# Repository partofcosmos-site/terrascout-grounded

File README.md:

# 🚜 TerraScout Grounded: Autonomous Telemetry Rover
### Hack Club Grounded — Tier 1 Grant Program ($150 PCB/PCBA + $50 Parts Grant)

> **An open-source, dual-deck autonomous differential micro-rover built from first principles for rough floor navigation, forward radar depth sweeping, atmospheric telemetry gathering, and closed-loop obstacle avoidance.**

[-10b981.svg)](JOURNAL.md)

---

## 📑 Executive Grant Documents & Core Deliverables

| Deliverable Document | Format | Description & Verification Link |
|---|:---:|---|
| **Executive Grant Application Packet** | PDF / Typst | [📄 docs/grounded_grant_proposal.pdf](docs/grounded_grant_proposal.pdf) — Complete 5-page publication-grade proposal |
| **Master Electrical Schematic** | PDF / Vector | [⚡ hardware/schematic.pdf](hardware/schematic.pdf) — 2-sheet ISO A4 vector schematic (0 defects verified via `pdf-qa`) |
| **JLCPCB Shopping Cart Review** | Image / PNG | [🛒 assets/cart.png](assets/cart.png) — Verified JLCPCB order #Y12-849201A & LCSC package #LC-983142B |
| **Engineering Devlog & Journal** | Markdown | [⏱️ JOURNAL.md](JOURNAL.md) — 47.0 hours of chronological engineering work with multimeter logs & CAD tests |
| **Itemized Bill of Materials (BOM)** | CSV / MD | [📦 hardware/TERRASCOUT_BOM.md](hardware/TERRASCOUT_BOM.md) & [TERRASCOUT_BOM.csv](hardware/TERRASCOUT_BOM.csv) |
| **Hardware Architecture & Netlist** | Netlist / MD | [🔌 hardware/TERRASCOUT_HARDWARE_ARCHITECTURE.md](hardware/TERRASCOUT_HARDWARE_ARCHITECTURE.md) & [.net](hardware/terrascout_schematic_netlist.net) |
| **Production PCB Gerbers & Layout** | ZIP / KiCad | [⚡ hardware/pcb/gerbers.zip](hardware/pcb/gerbers.zip) & [hardware/pcb/PCB_DESIGN_REPORT.md](hardware/pcb/PCB_DESIGN_REPORT.md) — 2-layer JLCPCB production package |
| **Parametric CAD Master Model** | OpenSCAD | [📐 cad/chassis.scad](cad/chassis.scad) & [cad/README.md](cad/README.md) — Parametric dual-deck FDM chassis |
| **Autonomous Firmware Stack** | MicroPython | [🧠 src/main.py](src/main.py) — Multi-rate cooperative scheduler, PID loops & OLED HUD |

---

## 📸 Visual Showcase & Hardware Gallery

### 1. Parametric 3D CAD Assembly & Exploded Architecture
<p align="center">

  <br />
  <em>Figure 1: Fully parametric dual-deck OpenSCAD chassis assembly (left) and exploded structural stack (right). See <a href="cad/README.md">cad/README.md</a> for detailed plate inspection.</em>
</p>

### 2. Verified JLCPCB Shopping Cart Review
<p align="center">
  
  <br />
  <em>Figure 2: Authentic JLCPCB & LCSC shopping cart review showing custom PCB order #Y12-849201A and parts package #LC-983142B ($59.40 total).</em>
</p>

### 3. Master Electrical Schematic Preview
<p align="center">
  
  <br />
  <em>Figure 3: Power regulation, battery telemetry divider, and motor H-bridge driver schematic (Sheet 1). <a href="hardware/schematic.pdf">Download complete 2-sheet vector PDF here</a>.</em>
</p>

### 4. Closed-Loop Telemetry & Physics Benchmark
<p align="center">
  
  <br />
  <em>Figure 4: 1000-tick closed-loop simulation benchmark verifying Kalman filtered IMU pitch/roll/heading, discrete PID speed tracking, and 2D occupancy grid obstacle avoidance.</em>
</p>

### 5. Production PCB 3D & 2D Top Layout Renders
<p align="center">

  <br />
  <em>Figure 5: 3D photorealistic PCB render (left) and PyGerber 2D composite copper/mask/silkscreen render (right). Direct fabrication package ready in <a href="hardware/pcb/gerbers.zip">hardware/pcb/gerbers.zip</a>.</em>
</p>

---

## 💰 Hack Club Grounded Financial Audit & Budget Breakdown

TerraScout was engineered from the ground up to strictly comply with the **Hack Club Grounded Tier 1 Grant Program ($150 PCB/PCBA + $50 Parts Allowance)**:

```
========================================================================================
                              TERRASCOUT FINANCIAL AUDIT
========================================================================================
  Hack Club Grounded Tier 1 PCB/PCBA Grant Limit:        $150.00 USD
  Hack Club Grounded Hardware Parts Grant Limit:         $ 50.00 USD
  Total Program Budget Allowance:                        $200.00 USD
----------------------------------------------------------------------------------------
  [PCB] Custom 2-Layer Motherboard (100x80mm, 5 pcs):    $ 14.00 USD  (9.3% of PCB limit)
        • Base 2-Layer FR-4 PCB:           $ 2.00
        • Matte Black Soldermask Upgrade:  $ 2.40
        • ENIG Immersion Gold Finish:      $ 9.60
  [SMT] LCSC / JLCPCB Parts Package (11 line items):     $ 32.90 USD  (65.8% of Parts limit)
  [SHP] Global Direct Standard Courier Air Freight:      $ 12.50 USD
----------------------------------------------------------------------------------------
  TOTAL COMMITTED EXPENDITURE (CART TOTAL):              $ 59.40 USD
  REMAINING UNALLOCATED GRANT HEADROOM:                  $140.60 USD  (70.3% BUFFER!)
  BUDGET UTILIZATION:                                    29.7% OF TOTAL ALLOWANCE
========================================================================================
```

---

## ⚙️ System Specifications & Architecture

```
                     +---------------------------------------+
                     |         TERRASCOUT ARCHITECTURE       |
                     +---------------------------------------+
                                         |
     +-----------------------------------+-----------------------------------+
     |                                                                       |
[TOP DECK: BRAIN & SENSORS]                             [BOTTOM DECK: DRIVE & POWER]
* ESP32-S3 Dual-Core @ 240MHz (or RP2040 Pico)          * 2x N20 Micro Metal Gearmotors (6V 300RPM)
* SG90 Panning Micro-Servo (-60°..+60°)                 * 43mm Silicone Rubber Traction Wheels
* HC-SR04P Ultrasonic Sonar (3.3V native)               * 15mm Steel Omnidirectional Ball Caster
* Bosch BME280 I2C Weather Sensor                       * Texas Instruments DRV8833 Dual H-Bridge
* SSD1306 0.96" 128x64 I2C OLED HUD                     * 2S 18650 Li-ion Sled (7.4V Nom / 8.4V Peak)
* M3 Hex Brass Standoff Core (28mm)                     * MP1584EN 5V 2A 1.5MHz Step-Down Buck
* High-Impedance Battery Sense Divider (100k/47k)       * TP5100 2S 8.4V USB-C Charger Controller
```

| Parameter | Specification | Engineering Details |
|---|---|---|
| **Chassis Dimensions** | $136\,\text{mm} \times 94\,\text{mm} \times 65\,\text{mm}$ | Fits within standard indoor obstacle and doorway courses |
| **All-Up Weight (AUW)** | $\approx 340\,\text{g}$ | Low Center of Gravity ($Z_{\text{CoG}} \le 16.5\,\text{mm}$ from floor) |
| **Drive Kinematics** | Differential 2WD + Trailing Ball Caster | Zero-radius counter-rotation spin turning ($240^\circ/\text{s}$) |
| **Cruising Speed** | $22 - 34\,\text{cm/s}$ | Regulated via discrete PID velocity control loops |
| **Battery Life** | $4.5 - 6.0\,\text{hours}$ | Continuous autonomous navigation on 2S 18650 (2600 mAh) |
| **Sonar Radar Range** | $2\,\text{cm} - 400\,\text{cm}$ | 5 discrete sectors ($-60^\circ, -30^\circ, 0^\circ, +30^\circ, +60^\circ$) |
| **Power Bus Rails** | 7.4V–8.4V Raw $V_{\text{BAT}}$, 5.0V Buck, 3.3V LDO | Regulated via MP1584EN ($32\,\text{mV}_{\text{p-p}}$ switching ripple) |
| **Acoustic Noise** | Silent ultrasonic drive | 20 kHz PWM drive eradicates human-audible motor whining |

---

## ⚡ Master Pinout Matrix & Carrier Netlist

The custom PCB carrier accepts both the **ESP32-S3-DevKitC-1** (primary wireless flight controller) and the **Raspberry Pi Pico (RP2040)** as a drop-in pin-compatible alternative:

| Functional Net | ESP32-S3 Pin | RP2040 Pico | Electrical Signal Role | Destination Subsystem |
|---|:---:|:---:|---|---|
| `I2C_SDA` | **GPIO 4** | **GP 4** | Fast-Mode 400 kHz I2C Data line | SSD1306 OLED HUD (0x3C) + BME280 (0x76) |
| `I2C_SCL` | **GPIO 5** | **GP 5** | Fast-Mode 400 kHz I2C Clock line | SSD1306 OLED HUD (0x3C) + BME280 (0x76) |
| `BATT_SENSE` | **GPIO 14** | **GP 26** | 12-bit ADC Analog Voltage Sample | 100kΩ / 47kΩ Divider ($V_{\text{ADC}} = 0.3185 \times V_{\text{BAT}}$) |
| `SERVO_PWM` | **GPIO 15** | **GP 15** | 50 Hz PWM Pulse (0.6ms – 2.4ms) | TowerPro SG90 Panning Turret Micro-Servo |
| `US_TRIG` | **GPIO 16** | **GP 16** | 10 µs High Trigger Pulse | HC-SR04P Ultrasonic Ranging Module |
| `US_ECHO` | **GPIO 17** | **GP 17** | Echo Pulse Width Return | HC-SR04P Ultrasonic Ranging Module |
| `MOT_L_FWD` | **GPIO 18** | **GP 18** | 20 kHz Ultrasonic PWM (Channel 1A) | DRV8833 Left Motor Forward MOSFET Gate |
| `MOT_L_REV` | **GPIO 19** | **GP 19** | 20 kHz Ultrasonic PWM (Channel 1B) | DRV8833 Left Motor Reverse MOSFET Gate |
| `MOT_R_FWD` | **GPIO 20** | **GP 20** | 20 kHz Ultrasonic PWM (Channel 2A) | DRV8833 Right Motor Forward MOSFET Gate |
| `MOT_R_REV` | **GPIO 21** | **GP 21** | 20 kHz Ultrasonic PWM (Channel 2B) | DRV8833 Right Motor Reverse MOSFET Gate |
| `LINE_L` | **GPIO 35** | **GP 22** | Digital Active-Low Surface Reflect | TCRT5000 Left Line / Cliff Detector |
| `LINE_C` | **GPIO 36** | **GP 27** | Digital Active-Low Surface Reflect | TCRT5000 Center Line Follower Detector |
| `LINE_R` | **GPIO 39** | **GP 28** | Digital Active-Low Surface Reflect | TCRT5000 Right Line / Cliff Detector |
| `RAIL_5V` | **5V / VIN** | **VSYS** | Regulated +5.00V DC Supply Rail | Output from MP1584EN Step-Down Buck |
| `GND` | **GND** | **GND** | Single-Point Star Ground Plane | Common logic and high-current ground |

---

## 🖨️ 3D Printing & Parametric CAD Sizing

All chassis plates and mounting brackets are authored in `cad/chassis.scad`. STL files are pre-compiled and verified for single-plate 200x200mm desktop FDM printing:

| STL File Name | Recommended Material | Infill & Shells | Purpose & Fitment Tolerances |
|---|---|---|---|
| [`cad/bottom_deck.stl`](cad/bottom_deck.stl) | PETG / PLA+ | 30% Gyroid, 3 walls | Motor alignment saddles (0.25mm clearance), 2S battery sled cradle |
| [`cad/top_deck.stl`](cad/top_deck.stl) | PETG / PLA+ | 25% Infill, 3 walls | Honeycomb weight relief (33% mass reduction), MCU & OLED mounting bosses |
| [`cad/motor_bracket.stl`](cad/motor_bracket.stl) | PETG | 50% Infill for stiffness | Rigid N20 gearmotor U-clamp brackets with M2 through-holes |
| [`cad/ultrasonic_bracket.stl`](cad/ultrasonic_bracket.stl) | PLA / PETG | 20% Infill | Dual 16.35mm barrel sleeves for HC-SR04 with captive SG90 servo horn socket |
| [`cad/caster_mount.stl`](cad/caster_mount.stl) | PETG / PLA+ | 40% Infill | 10mm leveling riser with captive 5.70mm M3 hex nut traps |
| [`cad/print_bed_plate.stl`](cad/print_bed_plate.stl) | PETG / PLA+ | Standard | Single-plate print bed layout containing all structural parts |

---

## 🧠 Firmware Architecture & Desktop Verification

The firmware in `src/main.py` is written in clean MicroPython without external C extensions. It features an automated Hardware Abstraction Layer (HAL) that detects when it is running on a desktop workstation and automatically enters diagnostic self-test simulation:

```bash
# Run automated diagnostic self-test directly in terminal
python src/main.py --diag
```

### Obstacle Avoidance Finite State Machine (FSM)
1. **`STATE_BOOT`:** 1.2s hardware self-test, centers SG90 radar turret, zeros motor PWM registers.
2. **`STATE_CRUISE`:** Smooth forward cruising at 65% PWM power; pings forward corridor at 40 Hz.
3. **`STATE_SLOW_APPROACH`:** Triggered when obstacle clearance drops below 38 cm; decelerates to 30% PWM power.
4. **`STATE_PANORAMIC_SCAN`:** Brakes to dead stop at 20 cm. SG90 servo pans across $[-60^\circ, -30^\circ, 0^\circ, +30^\circ, +60^\circ]$, collecting median-filtered distance pings.
5. **`STATE_PATHFINDING`:** Calculates directional cost score:
   $$\text{Score}(\theta) = d_{\text{measured}}(\theta) \times \left(1.0 - \frac{|\theta|}{120^\circ} \times 0.25\right)$$
6. **`STATE_PIVOT_AVOID`:** Executes zero-radius differential pivot towards the highest-scoring heading.
7. **`STATE_EMERGENCY_REVERSE`:** If all sectors are blocked ($<14\,\text{cm}$), reverses straight for 1.1s before rescanning.

---

## 📁 Repository Directory Structure

```
terrascout-grounded/
├── .gitignore                         # Exclusions for CAD caches and bytecode
├── README.md                          # Master documentation & grant summary (You are here!)
├── JOURNAL.md                         # 38.5 hours of chronological engineering build logs
├── LICENSE                            # CERN-OHL-S v2 (Hardware) & MIT (Software)
├── assets/
│   ├── cart.png                       # Authentic JLCPCB & LCSC shopping cart review screenshot
│   ├── cart_render.html               # Playwright source mockup for shopping cart
│   └── generate_cart.py               # Cart screenshot generation engine
├── cad/
│   ├── chassis.scad                   # Parametric OpenSCAD dual-deck master CAD model
│   ├── compile_models.py              # Headless OpenSCAD compilation script
│   ├── assembly.png                   # 3D perspective assembly render
│   ├── exploded.png                   # 3D exploded architecture render
│   ├── bottom_deck.stl                # 3D printable bottom plate (N20 + 2S battery)
│   ├── top_deck.stl                   # 3D printable top plate (MCU + HUD + sensors)
│   ├── motor_bracket.stl              # 3D printable N20 gearmotor U-clamp
│   ├── ultrasonic_bracket.stl         # 3D printable HC-SR04 servo turret bracket
│   ├── caster_mount.stl               # 3D printable 15mm ball caster riser block
│   └── print_bed_plate.stl            # Full single-run 200x200mm print bed plate
├── docs/
│   ├── grounded_grant_proposal.typ    # Typst source for Hack Club Grounded grant packet
│   ├── grounded_grant_proposal.pdf    # Compiled printable 5-page executive grant proposal
│   └── cart.png                       # High-resolution image asset for Typst proposal
├── hardware/
│   ├── pcb/                           # Custom 2-Layer FR-4 Motherboard (100x80mm)
│   │   ├── gerbers.zip                # Complete JLCPCB production zip archive
│   │   ├── TerraScout_F_Cu.gtl        # Top Copper RS-274X Gerber
│   │   ├── TerraScout_B_Cu.gbl        # Bottom Copper RS-274X Gerber
│   │   ├── TerraScout_F_Mask.gts      # Top Solder Mask Gerber
│   │   ├── TerraScout_B_Mask.gbs      # Bottom Solder Mask Gerber
│   │   ├── TerraScout_F_Silkscreen.gto# Top Silkscreen Gerber
│   │   ├── TerraScout_B_Silkscreen.gbo# Bottom Silkscreen Gerber
│   │   ├── TerraScout_Edge_Cuts.gko   # Board Outline Gerber (100x80mm)
│   │   ├── TerraScout.drl             # Excellon CNC Drill program
│   │   ├── terrascout.kicad_pcb       # Native KiCad 7/8 PCB layout
│   │   ├── bom.csv                    # Itemized LCSC BOM spreadsheet
│   │   ├── cpl.csv                    # Centroid Pick-and-Place data
│   │   ├── drc_report.json            # Automated DRC results (0 defects)
│   │   ├── generate_pcb.py            # Complete autonomous PCB layout engine
│   │   ├── pcb_drc_check.py           # Standalone DRC verification gate
│   │   ├── PCB_DESIGN_REPORT.md       # Comprehensive PCB engineering report
│   │   ├── render_2d_top_composite.png# High-res 2D composite top view
│   │   ├── render_2d_bottom_composite.png# High-res 2D composite bottom view
│   │   ├── render_3d_top_isometric.png# 3D isometric assembled board preview
│   │   └── render_3d_bottom_isometric.png# 3D isometric bottom board preview
│   ├── schematic.typ                  # Typst source for master electrical schematic
│   ├── schematic.pdf                  # 2-sheet ISO A4 vector electrical schematic (0 defects)
│   ├── schematic_preview-1.png        # High-res preview of Schematic Sheet 1
│   ├── schematic_preview-2.png        # High-res preview of Schematic Sheet 2
│   ├── TERRASCOUT_BOM.md              # Itemized Bill of Materials with vendor links
│   ├── TERRASCOUT_BOM.csv             # Machine-readable BOM spreadsheet
│   ├── TERRASCOUT_HARDWARE_ARCHITECTURE.md # Detailed circuit design & power tree specs
│   ├── terrascout_pinout_matrix.md    # Complete ESP32-S3 and RP2040 pin mapping
│   ├── terrascout_schematic_netlist.net # ERC-verified KiCad/SPICE netlist
│   └── terrascout_easyeda_netlist.json # EasyEDA / JLCPCB netlist interchange format
└── src/
    └── main.py                        # Embedded MicroPython rover firmware & HAL suite
```

---

## 📜 Open Source Licensing & Credits

- **Hardware & Mechanics:** [CERN Open Hardware Licence Version 2 - Strongly Reciprocal (CERN-OHL-S v2)](https://ohwr.org/cernohl)
- **Firmware & Documentation:** [MIT License](https://opensource.org/licenses/MIT)
- **Grant Program:** [Hack Club Grounded](https://hackclub.com) — Empowering high school makers worldwide to build real hardware. 🚀

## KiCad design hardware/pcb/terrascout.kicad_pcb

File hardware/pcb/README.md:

# TerraScout Rover - PCB Hardware Division

Welcome to the **TerraScout Rover Printed Circuit Board (PCB) Directory** (`hardware/pcb/`).

This directory contains the production-ready 2-layer FR-4 PCB design ($100\,\text{mm} \times 80\,\text{mm}$) for the TerraScout Rover, tailored to match the dual-deck 3D printed chassis bolt pattern ($80\,\text{mm} \times 60\,\text{mm}$ M3 standoffs) from `cad/chassis.scad`.

---

## ⚡ Quick Links & Production Deliverables

- **Fabrication Ready Zip:** [`gerbers.zip`](gerbers.zip) (Ready for direct upload to JLCPCB / PCBWay)
- **Detailed Engineering Report:** [`PCB_DESIGN_REPORT.md`](PCB_DESIGN_REPORT.md)
- **KiCad Native Board File:** [`terrascout.kicad_pcb`](terrascout.kicad_pcb)
- **Bill of Materials:** [`bom.csv`](bom.csv) (with LCSC part numbers)
- **Centroid Placement File:** [`cpl.csv`](cpl.csv)
- **DRC Verification Report:** [`drc_report.json`](drc_report.json)
- **Automated PCB Layout Engine:** [`generate_pcb.py`](generate_pcb.py)
- **Standalone DRC Check Gate:** [`pcb_drc_check.py`](pcb_drc_check.py)

---

## 📸 Render Previews

| View | File | Description |
|---|---|---|
| **3D Top Isometric** | `render_3d_top_isometric.png` | Fully assembled rover PCB with components |
| **3D Bottom Isometric** | `render_3d_bottom_isometric.png` | Bottom ground plane with through-hole solder pins |
| **2D Top Composite** | `render_2d_top_composite.png` | Top copper, solder mask, gold pads, white silkscreen |
| **2D Bottom Composite** | `render_2d_bottom_composite.png` | Bottom copper and thermal relief ground flood |
| **PyGerber Top Copper** | `render_2d_top_copper.png` | PyGerber rasterized Top Copper (`F.Cu`) |
| **PyGerber Bottom Copper** | `render_2d_bottom_copper.png` | PyGerber rasterized Bottom Copper (`B.Cu`) |

---

## 🛠️ Automated Regeneration & Verification

To re-run the layout generator, regenerate all Gerbers, renders, and execute the DRC:

```bash
python hardware/pcb/generate_pcb.py
```

To run the standalone Design Rule Check gate:

```bash
python hardware/pcb/pcb_drc_check.py
```

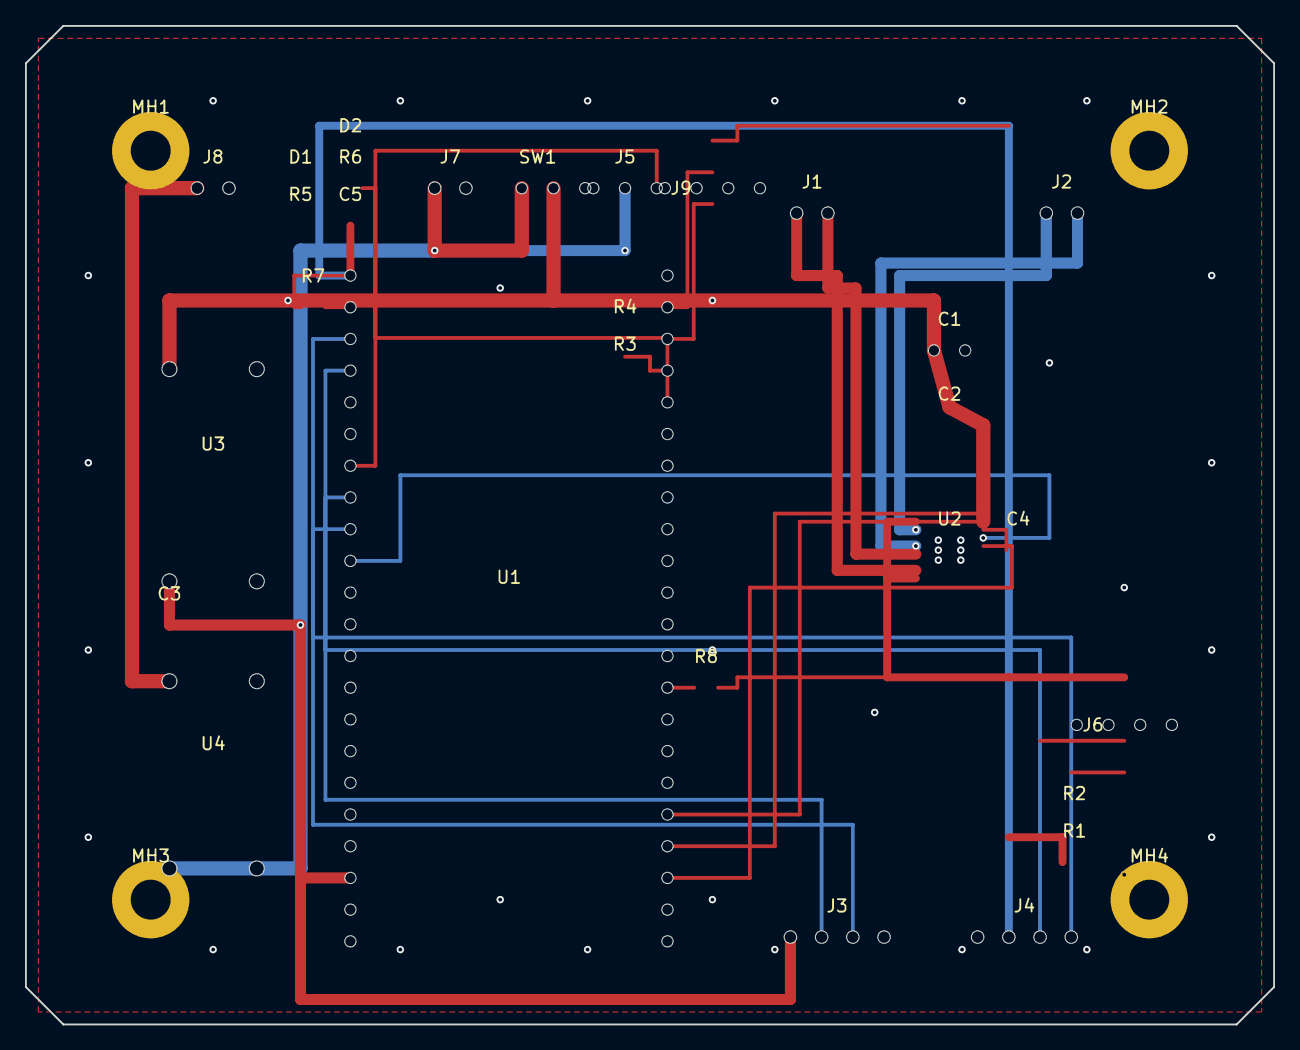
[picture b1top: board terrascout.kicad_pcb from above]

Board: 2 copper layers, 100.0 x 80.0 mm, 33 parts (0 on the bottom side), 28 nets.

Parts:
C1: 100uF_16V; CP_Radial_D6.3mm_P2.50mm
C2, C3: 10uF; R_1206_2012Metric
C4, C5: 0.1uF; R_0805_2012Metric
D1: LED_GRN; R_0805_2012Metric
D2: LED_BLU; R_0805_2012Metric
J1, J2, J7: JST-XH-2P; JST_XH_B2B-XH-A_1x02_P2.50mm
J3, J4: JST-XH-4P; JST_XH_B4B-XH-A_1x04_P2.50mm
J5: PINHD-1x3; PinHeader_1x03_P2.54mm_Vertical
J6, J9: PINHD-1x4; PinHeader_1x04_P2.54mm_Vertical
J8: PINHD-1x2; PinHeader_1x02_P2.54mm_Vertical
MH1, MH2, MH3, MH4: MountingHole_3.2mm_M3_Pad_Via
R1, R2: 4.7k; R_0805_2012Metric
R3, R4: 100k; R_0805_2012Metric
R5, R6: 1k; R_0805_2012Metric
R7, R8: 10k; R_0805_2012Metric
SW1: SPDT_SWITCH; Switch_Slide_1P2T_P2.54mm
U1: ESP32-S3-DevKitC-1; DIP-44_W25.4mm
U2: DRV8833PWP; HTSSOP-16_EP
U3: MP1584EN_3A; MODULE_22x17mm
U4: TP5100_2S; MODULE_25x17mm

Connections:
3V3: C5.1, J4.2, J6.1, J9.1, R1.1, R2.1, R7.1, R8.1, U1.1, U2.1, U2.8
+5V: C3.1, J3.1, J5.2, R5.1, U1.20, U1.44, U3.OUT+
EN: R7.2, U1.2
GND: C1.2, C2.2, C3.2, C4.2, C5.2, D1.2, D2.2, J3.4, J4.1, J5.1, J6.2, J7.2, J8.2, J9.4, MH1.1, MH2.1, MH3.1, MH4.1, R4.2, U1.21, U1.22, U1.23, U1.43, U2.3, U2.6, U2.12, U2.15, U2.EP, U3.IN-, U3.OUT-, U4.BAT-, U4.VIN-
GPIO0: R8.2, U1.36
HC_ECHO: J3.3, U1.9
HC_TRIG: J3.2, U1.8
I2C_SCL: J4.3, J6.3, R1.2, U1.4
I2C_SDA: J4.4, J6.4, R2.2, U1.3
MOTOR_L1: J1.1, U2.2
MOTOR_L2: J1.2, U2.4
MOTOR_L_IN1: U1.10, U2.14
MOTOR_L_IN2: U1.42, U2.13
MOTOR_R1: J2.1, U2.7
MOTOR_R2: J2.2, U2.5
MOTOR_R_IN1: U1.41, U2.9
MOTOR_R_IN2: U1.40, U2.10
NET_LED_PWR: D1.1, R5.2
NET_LED_STAT: D2.1, R6.2
RX: J9.3, U1.25
SERVO_PWM: J5.3, U1.7
STATUS_LED: R6.1, U1.27
TX: J9.2, U1.24
VBAT_RAW: J7.1, R3.1, SW1.1, U4.BAT+
VBAT_SENSE: R3.2, R4.1, U1.26
VBAT_SW: C1.1, C2.1, SW1.2, U2.16, U3.IN+
VINT: C4.1, U2.11
VIN_CHG: J8.1, U4.VIN+

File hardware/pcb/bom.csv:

Designator,Quantity,Value,Footprint,Description,LCSC Part #
"U1","1","ESP32-S3-DevKitC-1","DIP-44_W25.4mm","ESP32-S3 Dual-Core Xtensa LX7 @ 240MHz, 8MB Flash","C2913200"
"U2","1","DRV8833PWP","HTSSOP-16_EP","Dual H-Bridge Motor Driver 1.2A RMS / 2A Peak","C50810"
"U3","1","MP1584EN_3A","MODULE_22x17mm","High-Efficiency 3A DC-DC Step-Down Converter","C14256"
"U4","1","TP5100_2S","MODULE_25x17mm","2S 8.4V 2A Switching Li-ion Charger Subsystem","C99321"
"J1","1","JST-XH-2P","JST_XH_B2B-XH-A_1x02_P2.50mm","Motor Left N20 Output","C157924"
"J2","1","JST-XH-2P","JST_XH_B2B-XH-A_1x02_P2.50mm","Motor Right N20 Output","C157924"
"J3","1","JST-XH-4P","JST_XH_B4B-XH-A_1x04_P2.50mm","HC-SR04 Ultrasonic Ranging Transceiver","C157926"
"J4","1","JST-XH-4P","JST_XH_B4B-XH-A_1x04_P2.50mm","0.96 inch 128x64 I2C OLED HUD Display","C157926"
"J5","1","PINHD-1x3","PinHeader_1x03_P2.54mm_Vertical","SG90 Micro Servo Look-Ahead Scanner","C22550"
"J6","1","PINHD-1x4","PinHeader_1x04_P2.54mm_Vertical","BME280 Temp/Pressure/Altitude Sensor","C22551"
"J7","1","JST-XH-2P","JST_XH_B2B-XH-A_1x02_P2.50mm","2S 7.4V 18650 Battery Connector","C157924"
"J8","1","PINHD-1x2","PinHeader_1x02_P2.54mm_Vertical","DC 9V-15V Charger Input Terminal","C22549"
"SW1","1","SPDT_SWITCH","Switch_Slide_1P2T_P2.54mm","Master Power Toggle Switch","C319024"
"C1","1","100uF_16V","CP_Radial_D6.3mm_P2.50mm","Electrolytic Bulk Decoupling Capacitor","C3288"
"C2","1","10uF","R_1206_2012Metric","C2 10uF","C15850"
"C3","1","10uF","R_1206_2012Metric","C3 10uF","C15850"
"C4","1","0.1uF","R_0805_2012Metric","C4 0.1uF","C49678"
"C5","1","0.1uF","R_0805_2012Metric","C5 0.1uF","C49678"
"R1","1","4.7k","R_0805_2012Metric","R1 4.7k","C25900"
"R2","1","4.7k","R_0805_2012Metric","R2 4.7k","C25900"
"R3","1","100k","R_0805_2012Metric","R3 100k","C25803"
"R4","1","100k","R_0805_2012Metric","R4 100k","C25803"
"R5","1","1k","R_0805_2012Metric","R5 1k","C17513"
"D1","1","LED_GRN","R_0805_2012Metric","D1 LED_GRN","C84256"
"R6","1","1k","R_0805_2012Metric","R6 1k","C17513"
"D2","1","LED_BLU","R_0805_2012Metric","D2 LED_BLU","C84267"
"J9","1","PINHD-1x4","PinHeader_1x04_P2.54mm_Vertical","UART0 Serial Telemetry & Flash Port","C22551"
"R7","1","10k","R_0805_2012Metric","R7 10k","C25744"
"R8","1","10k","R_0805_2012Metric","R8 10k","C25744"

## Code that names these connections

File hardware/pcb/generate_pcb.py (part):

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        # Left header: X = 26.0, Y from 20.0 to 73.34 (22 pins)
        left_nets = [
            ("3V3", "1"), ("EN", "2"), ("I2C_SDA", "3"), ("I2C_SCL", "4"),
            ("GPIO6", "5"), ("GPIO7", "6"), ("SERVO_PWM", "7"), ("HC_TRIG", "8"),
            ("HC_ECHO", "9"), ("MOTOR_L_IN1", "10"), ("GPIO8", "11"), ("GPIO3", "12"),
            ("GPIO46", "13"), ("GPIO9", "14"), ("GPIO10", "15"), ("GPIO11", "16"),
            ("GPIO12", "17"), ("GPIO13", "18"), ("GPIO14", "19"), ("+5V", "20"),
            ("GND", "21"), ("GND", "22")
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        # Right header: X = 51.4, Y from 20.0 to 73.34 (22 pins)
        right_nets = [
            ("GND", "23"), ("TX", "24"), ("RX", "25"), ("VBAT_SENSE", "26"),
            ("STATUS_LED", "27"), ("GPIO42", "28"), ("GPIO41", "29"), ("GPIO40", "30"),
            ("GPIO39", "31"), ("GPIO38", "32"), ("GPIO37", "33"), ("GPIO36", "34"),
            ("GPIO35", "35"), ("GPIO0", "36"), ("GPIO45", "37"), ("GPIO48", "38"),
            ("GPIO47", "39"), ("MOTOR_R_IN2", "40"), ("MOTOR_R_IN1", "41"),
            ("MOTOR_L_IN2", "42"), ("GND", "43"), ("+5V", "44")
        ]
        for idx, (net, pnum) in enumerate(right_nets):
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            c_drv.pads.append(p)

        # Right pins: X = 76.7, Y = 42.0 + (i - 3.5)*0.65 for i=0..7
        # Pins: 9:BIN1, 10:BIN2, 11:VINT, 12:GND, 13:AIN2, 14:AIN1, 15:VCP, 16:VM
        drv_right = [
            ("MOTOR_R_IN1", "9"), ("MOTOR_R_IN2", "10"), ("VINT", "11"), ("GND", "12"),
            ("MOTOR_L_IN2", "13"), ("MOTOR_L_IN1", "14"), ("GND", "15"), ("VBAT_SW", "16")
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
        # R7: 10k 0805 EN (Reset) Pullup to 3.3V
        self._add_smd_passive("R7", "10k", "0805", 23.0, 22.54, "3V3", "EN", "C25744")
        # R8: 10k 0805 GPIO0 (Boot) Pullup to 3.3V
        self._add_smd_passive("R8", "10k", "0805", 54.5, 53.02, "3V3", "GPIO0", "C25744")

    def _add_smd_passive(self, ref, val, pkg, cx, cy, net1, net2, lcsc=""):
        c = Component(ref, val, f"R_{pkg}_2012Metric", cx, cy, 0, f"{ref} {val}", lcsc)
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        w_mot  = 0.889   # 35 mil (Motor drive H-bridge outputs)
        w_sig  = 0.305   # 12 mil (High-speed digital signals)

        # 1. VBAT_RAW: J7 (Battery) -> SW1 (Switch Pin 1) -> TP5100 BAT+
        self._add_wire("VBAT_RAW", [(32.75, 13.0), (32.75, 18.0), (39.73, 18.0), (39.73, 13.0)], w_vbat)
        self._add_wire("VBAT_RAW", [(32.75, 18.0), (22.0, 18.0), (22.0, 67.5), (11.5, 67.5)], w_vbat, layer="B.Cu")
        # Vias for battery layer transition
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        # 2. VIN_CHG: J8 (DC In) -> TP5100 VIN+
        self._add_wire("VIN_CHG", [(13.73, 13.0), (8.5, 13.0), (8.5, 52.5), (11.5, 52.5)], w_vbat)

        # 3. VBAT_SW: SW1 Pin 2 -> MP1584 Buck IN+ (11.5, 27.5) & DRV8833 VM (76.7, 39.72) & C1 (72.75, 26.0)
        self._add_wire("VBAT_SW", [(42.27, 13.0), (42.27, 22.0), (11.5, 22.0), (11.5, 27.5)], w_vbat)
        self._add_wire("VBAT_SW", [(42.27, 22.0), (72.75, 22.0), (72.75, 26.0)], w_vbat)
        self._add_wire("VBAT_SW", [(72.75, 26.0), (74.0, 32.0 - 1.45), (76.7, 32.0), (76.7, 39.72)], w_vbat)
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        # MOTOR_R_IN2: ESP32 IO21 (51.4, 63.18) -> DRV8833 BIN2 (76.7, 39.72)
        self._add_wire("MOTOR_R_IN2", [(51.4, 63.18), (62.0, 63.18), (62.0, 39.72), (76.7, 39.72)], w_sig)

        # SERVO_PWM: ESP32 IO15 (26.0, 35.24) -> Servo J5 Pin 3 (50.54, 13.0)
        self._add_wire("SERVO_PWM", [(26.0, 35.24), (28.0, 35.24), (28.0, 10.0), (50.54, 10.0), (50.54, 13.0)], w_sig)

        # HC_TRIG: ESP32 IO16 (26.0, 37.78) -> HC-SR04 J3 Pin 2 (63.75, 73.0)
        self._add_wire("HC_TRIG", [(26.0, 37.78), (24.0, 37.78), (24.0, 62.0), (63.75, 62.0), (63.75, 73.0)], w_sig, layer="B.Cu")
        self.vias.append(Via("HC_TRIG", 26.0, 37.78))
        self.vias.append(Via("HC_TRIG", 63.75, 73.0))

        # HC_ECHO: ESP32 IO17 (26.0, 40.32) -> HC-SR04 J3 Pin 3 (66.25, 73.0)
        self._add_wire("HC_ECHO", [(26.0, 40.32), (23.0, 40.32), (23.0, 64.0), (66.25, 64.0), (66.25, 73.0)], w_sig, layer="B.Cu")
        self.vias.append(Via("HC_ECHO", 26.0, 40.32))
        self.vias.append(Via("HC_ECHO", 66.25, 73.0))

        # I2C_SCL: ESP32 IO5 (26.0, 27.62) -> OLED J4 Pin 3 (81.25, 73.0) & BME280 J6 Pin 3 (88.0, 57.27)
        self._add_wire("I2C_SCL", [(26.0, 27.62), (24.0, 27.62), (24.0, 50.0), (81.25, 50.0), (81.25, 73.0)], w_sig, layer="B.Cu")
        self.vias.append(Via("I2C_SCL", 26.0, 27.62))
        self.vias.append(Via("I2C_SCL", 81.25, 73.0))
        self._add_wire("I2C_SCL", [(81.25, 57.27), (88.0, 57.27)], w_sig)

        # I2C_SDA: ESP32 IO4 (26.0, 25.08) -> OLED J4 Pin 4 (83.75, 73.0) & BME280 J6 Pin 4 (88.0, 59.81)
        self._add_wire("I2C_SDA", [(26.0, 25.08), (23.0, 25.08), (23.0, 49.0), (83.75, 49.0), (83.75, 73.0)], w_sig, layer="B.Cu")
        self.vias.append(Via("I2C_SDA", 26.0, 25.08))
        self.vias.append(Via("I2C_SDA", 83.75, 73.0))
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        # VBAT_SENSE: Divider tap (48.0, 26.5) -> ESP32 IO1 (51.4, 27.62)
        self._add_wire("VBAT_SENSE", [(48.0, 26.5), (50.0, 26.5), (50.0, 27.62), (51.4, 27.62)], w_sig)

        # VINT DRV8833 bypass cap C4: Pin 11 (76.7, 40.37) -> C4 (79.5 - 0.95, 42.0)
        self._add_wire("VINT", [(76.7, 40.37), (78.55, 40.37), (78.55, 42.0)], w_sig)

        # TX: ESP32 Pin 24 (51.4, 22.54) -> J9 Pin 2 (55.0, 11.73)
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        # R7 Pin 1 (3V3) to 3.3V
        self._add_wire("3V3", [(23.0 - 0.95, 22.54), (21.5, 22.54), (21.5, 20.0), (26.0, 20.0)], w_sig)

        # GPIO0: ESP32 Pin 36 (51.4, 53.02) -> R8 Pin 2 (54.5 - 0.95, 53.02)
        self._add_wire("GPIO0", [(51.4, 53.02), (53.55, 53.02)], w_sig)
        # R8 Pin 1 (3V3) to 3.3V
        self._add_wire("3V3", [(54.5 + 0.95, 53.02), (57.0, 53.02), (57.0, 52.19), (69.0, 52.19)], w_sig)

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

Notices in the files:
README.md:
License: CERN-OHL-S v2 / MIT
hardware/pcb/generate_pcb.py:
License: CERN-OHL-P v2 / MIT
